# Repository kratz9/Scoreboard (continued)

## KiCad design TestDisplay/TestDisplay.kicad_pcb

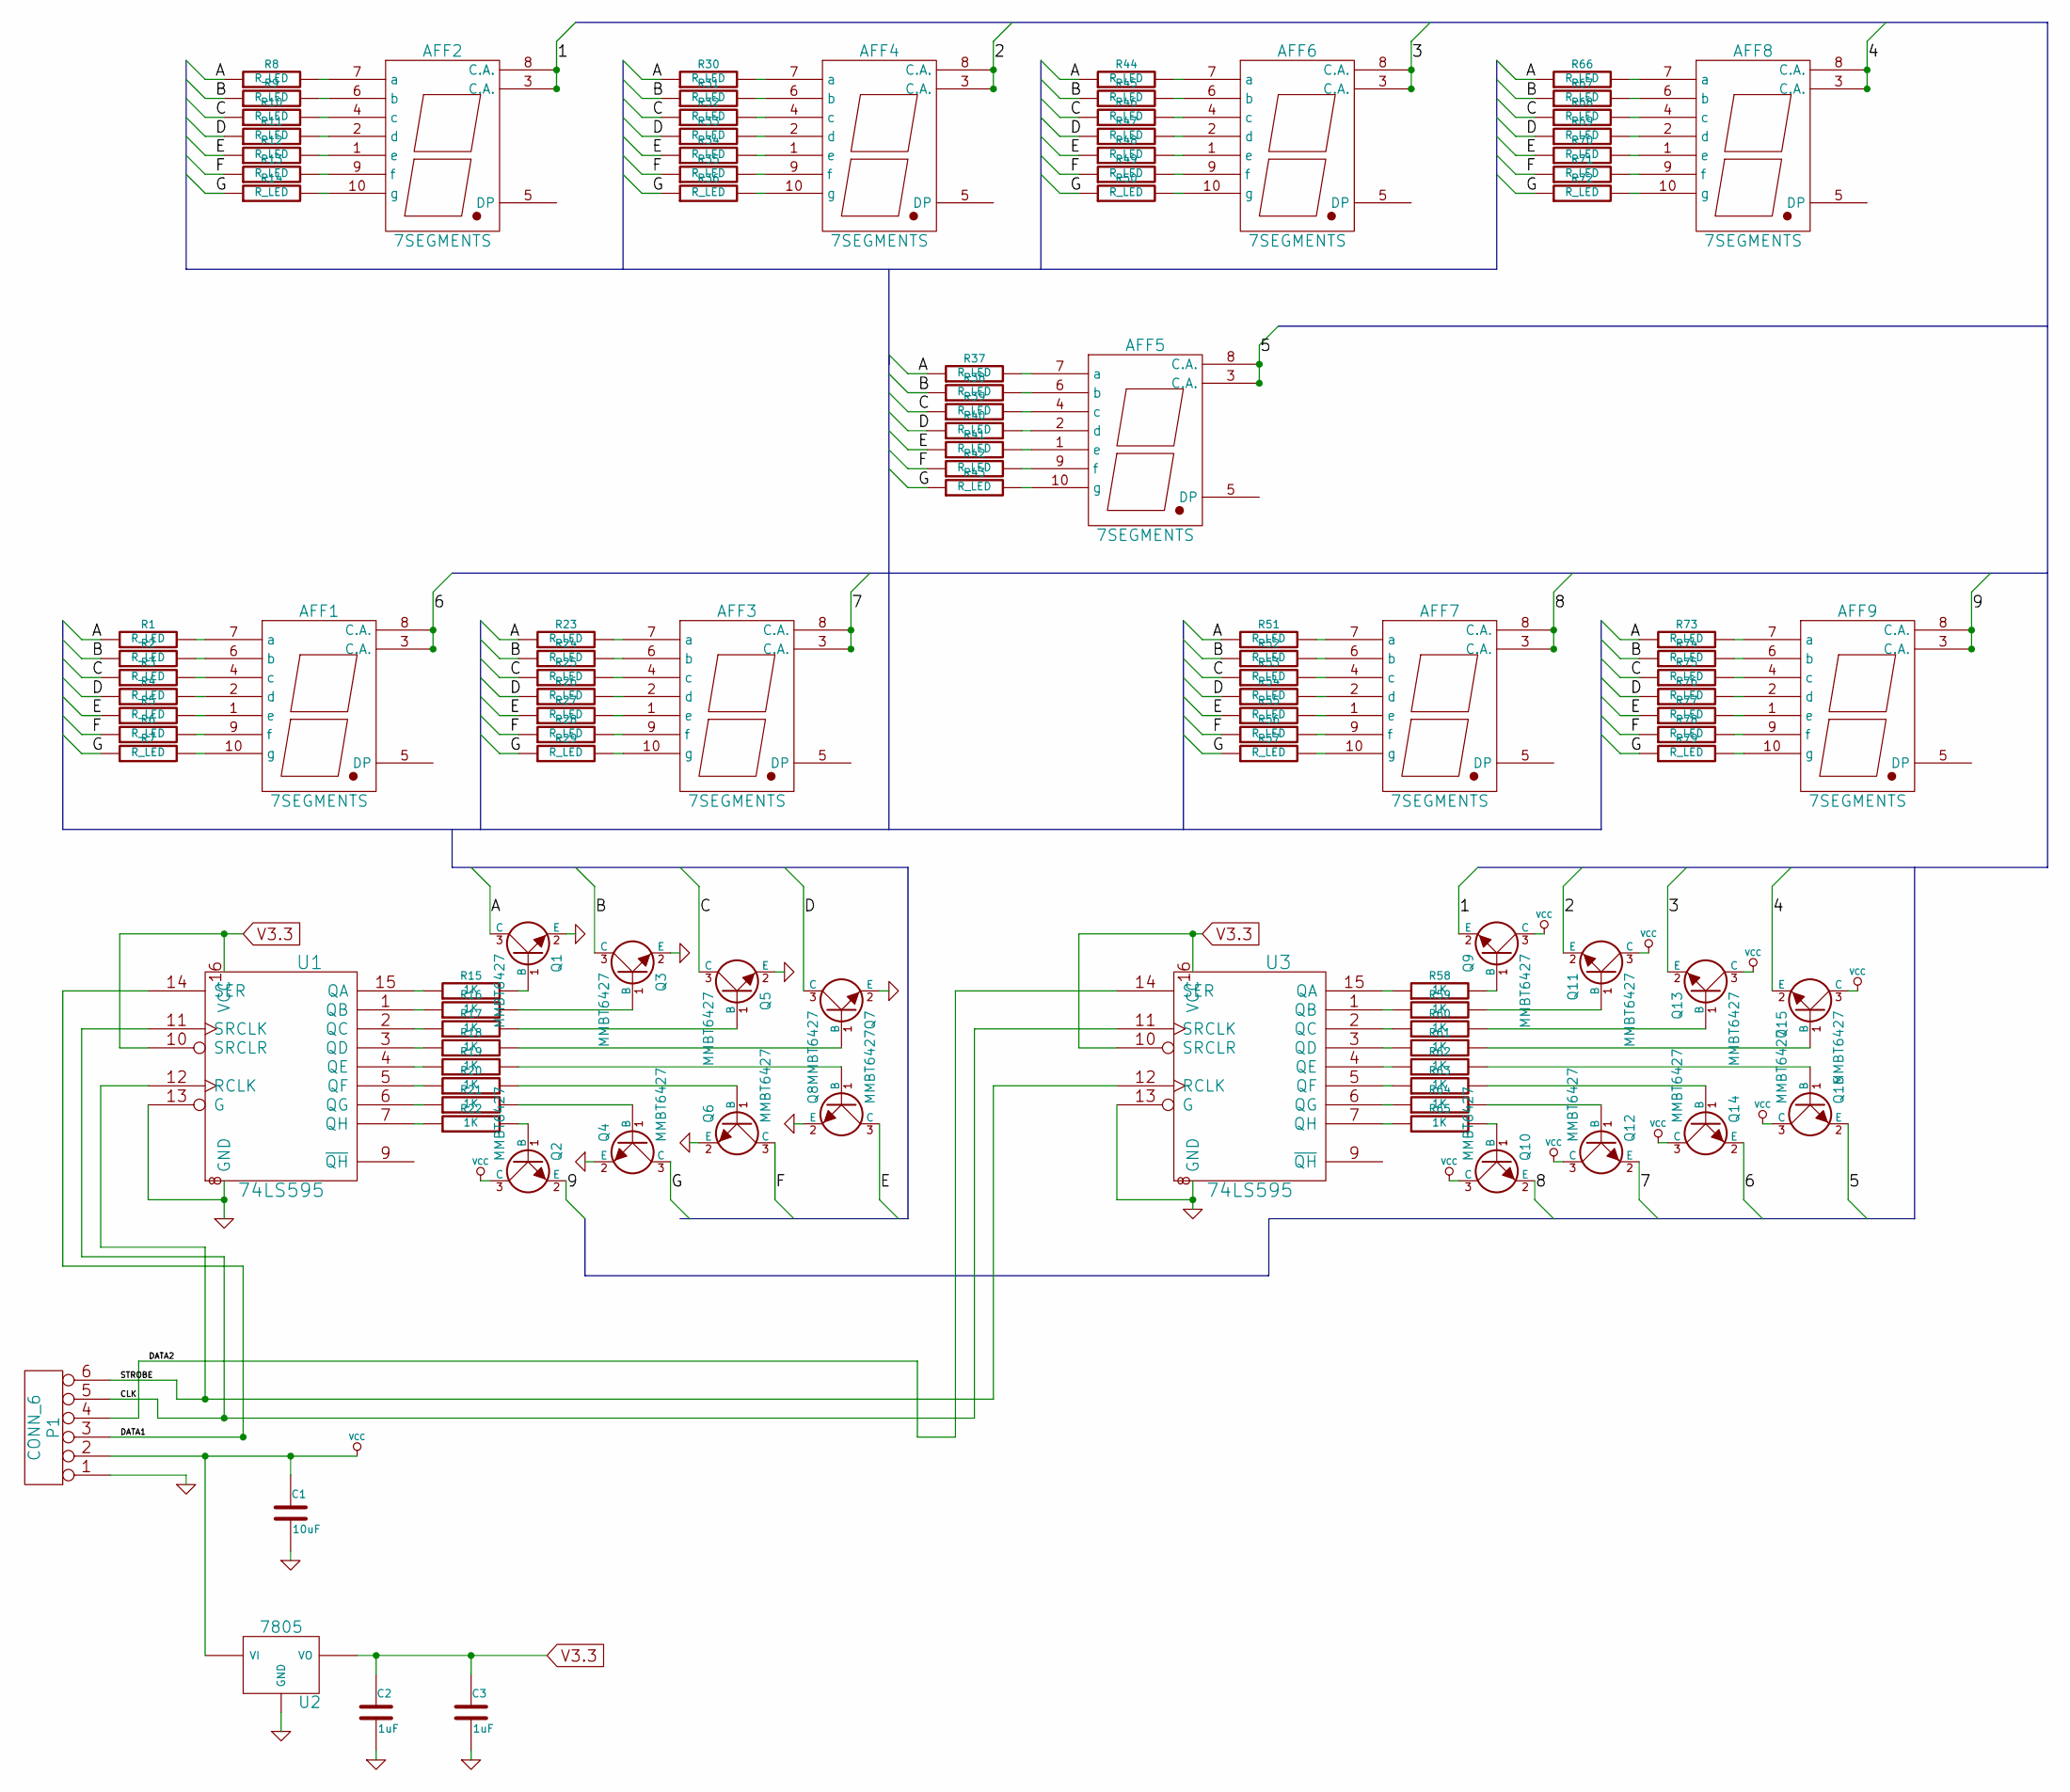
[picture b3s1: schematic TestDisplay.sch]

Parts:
AFF1, AFF2, AFF3, AFF4, AFF5, AFF6, AFF7, AFF8, AFF9: 7SEGMENTS
C1: 10uF
C2, C3: 1uF
P1: CONN_6
Q1, Q2, Q3, Q4, Q5, Q6, Q7, Q8, Q9, Q10, Q11, Q12, Q13, Q14, Q15, Q16: MMBT6427
R1, R2, R3, R4, R5, R6, R7, R8, R9, R10, R11, R12, R13, R14, R23, R24, R25, R26, R27, R28, R29, R30, R31, R32, R33, R34, R35, R36, R37, R38, R39, R40, R41, R42, R43, R44, R45, R46, R47, R48, R49, R50, R51, R52, R53, R54, R55, R56, R57, R66, R67, R68, R69, R70, R71, R72, R73, R74, R75, R76, R77, R78, R79: R_LED
R15, R16, R17, R18, R19, R20, R21, R22, R58, R59, R60, R61, R62, R63, R64, R65: 1K
U1, U3: 74LS595
U2: 7805

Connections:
/1: AFF2.3 (C.A.), AFF2.8 (C.A.), Q9.2 (E)
/2: AFF4.3 (C.A.), AFF4.8 (C.A.), Q11.2 (E)
/3: AFF6.3 (C.A.), AFF6.8 (C.A.), Q13.2 (E)
/4: AFF8.3 (C.A.), AFF8.8 (C.A.), Q15.2 (E)
/5: AFF5.3 (C.A.), AFF5.8 (C.A.), Q16.2 (E)
/6: AFF1.3 (C.A.), AFF1.8 (C.A.), Q14.2 (E)
/7: AFF3.3 (C.A.), AFF3.8 (C.A.), Q12.2 (E)
/8: AFF7.3 (C.A.), AFF7.8 (C.A.), Q10.2 (E)
/9: AFF9.3 (C.A.), AFF9.8 (C.A.), Q2.2 (E)
/A: Q1.3 (C), R1.1, R8.1, R23.1, R30.1, R37.1, R44.1, R51.1, R66.1, R73.1
/B: Q3.3 (C), R2.1, R9.1, R24.1, R31.1, R38.1, R45.1, R52.1, R67.1, R74.1
/C: Q5.3 (C), R3.1, R10.1, R25.1, R32.1, R39.1, R46.1, R53.1, R68.1, R75.1
/CLK: P1.5, U1.11 (SRCLK), U3.11 (SRCLK)
/D: Q7.3 (C), R4.1, R11.1, R26.1, R33.1, R40.1, R47.1, R54.1, R69.1, R76.1
/DATA1: P1.3, U1.14 (SER)
/DATA2: P1.4, U3.14 (SER)
/E: Q8.3 (C), R5.1, R12.1, R27.1, R34.1, R41.1, R48.1, R55.1, R70.1, R77.1
/F: Q6.3 (C), R6.1, R13.1, R28.1, R35.1, R42.1, R49.1, R56.1, R71.1, R78.1
/G: Q4.3 (C), R7.1, R14.1, R29.1, R36.1, R43.1, R50.1, R57.1, R72.1, R79.1
/STROBE: P1.6, U1.12 (RCLK), U3.12 (RCLK)
GND: C1.2, C2.2, C3.2, P1.1, Q1.2 (E), Q3.2 (E), Q4.2 (E), Q5.2 (E), Q6.2 (E), Q7.2 (E), Q8.2 (E), U1.8 (GND), U1.13 (G), U2.1, U2.GND, U3.8 (GND), U3.13 (G)
unnamed: AFF8.7 (a), R66.2
unnamed: AFF8.6 (b), R67.2
unnamed: AFF8.4 (c), R68.2
unnamed: AFF8.2 (d), R69.2
unnamed: AFF8.1 (e), R70.2
unnamed: AFF8.9 (f), R71.2
unnamed: AFF8.10 (g), R72.2
unnamed: AFF7.2 (d), R54.2
unnamed: AFF7.1 (e), R55.2
unnamed: AFF7.9 (f), R56.2
unnamed: AFF7.10 (g), R57.2
unnamed: AFF9.7 (a), R73.2
unnamed: AFF9.6 (b), R74.2
unnamed: AFF9.4 (c), R75.2
unnamed: AFF9.2 (d), R76.2
unnamed: AFF9.1 (e), R77.2
unnamed: AFF9.9 (f), R78.2
unnamed: AFF9.10 (g), R79.2
unnamed: AFF7.4 (c), R53.2
unnamed: AFF1.10 (g), R7.2
unnamed: AFF5.4 (c), R39.2
unnamed: AFF5.2 (d), R40.2
unnamed: AFF5.1 (e), R41.2
unnamed: AFF5.9 (f), R42.2
unnamed: AFF5.10 (g), R43.2
unnamed: AFF1.7 (a), R1.2
unnamed: AFF1.6 (b), R2.2
unnamed: AFF1.4 (c), R3.2
unnamed: AFF1.2 (d), R4.2
unnamed: AFF1.1 (e), R5.2
unnamed: AFF1.9 (f), R6.2
unnamed: AFF3.7 (a), R23.2
unnamed: AFF3.6 (b), R24.2
unnamed: AFF3.4 (c), R25.2
unnamed: AFF3.2 (d), R26.2
unnamed: AFF3.1 (e), R27.2
unnamed: AFF3.9 (f), R28.2
unnamed: AFF3.10 (g), R29.2
unnamed: AFF7.7 (a), R51.2
unnamed: AFF7.6 (b), R52.2
unnamed: Q13.1 (B), R60.2
unnamed: Q15.1 (B), R61.2
unnamed: Q16.1 (B), R62.2
unnamed: Q14.1 (B), R63.2
unnamed: Q12.1 (B), R64.2
unnamed: Q10.1 (B), R65.2
unnamed: Q11.1 (B), R59.2
unnamed: Q9.1 (B), R58.2
unnamed: R59.1, U3.1 (QB)
unnamed: R60.1, U3.2 (QC)
unnamed: R61.1, U3.3 (QD)
unnamed: R62.1, U3.4 (QE)
unnamed: R63.1, U3.5 (QF)
unnamed: R64.1, U3.6 (QG)
unnamed: R65.1, U3.7 (QH)
unnamed: R58.1, U3.15 (QA)
unnamed: Q1.1 (B), R15.2
unnamed: Q3.1 (B), R16.2
unnamed: Q5.1 (B), R17.2
unnamed: R19.1, U1.4 (QE)
unnamed: Q8.1 (B), R19.2
unnamed: R20.1, U1.5 (QF)
unnamed: Q6.1 (B), R20.2
unnamed: R21.1, U1.6 (QG)
unnamed: Q4.1 (B), R21.2
unnamed: R22.1, U1.7 (QH)
unnamed: Q2.1 (B), R22.2
unnamed: R15.1, U1.15 (QA)
unnamed: R16.1, U1.1 (QB)
unnamed: R17.1, U1.2 (QC)
unnamed: R18.1, U1.3 (QD)
unnamed: Q7.1 (B), R18.2
unnamed: AFF5.6 (b), R38.2
unnamed: AFF2.10 (g), R14.2
unnamed: AFF2.7 (a), R8.2
unnamed: AFF2.6 (b), R9.2
unnamed: AFF2.4 (c), R10.2
unnamed: AFF2.2 (d), R11.2
unnamed: AFF2.1 (e), R12.2
unnamed: AFF2.9 (f), R13.2
unnamed: AFF4.1 (e), R34.2
unnamed: AFF4.2 (d), R33.2
unnamed: AFF4.4 (c), R32.2
unnamed: AFF4.6 (b), R31.2
unnamed: AFF4.7 (a), R30.2
unnamed: AFF4.9 (f), R35.2
unnamed: AFF4.10 (g), R36.2
unnamed: AFF5.7 (a), R37.2
unnamed: AFF6.7 (a), R44.2
unnamed: AFF6.6 (b), R45.2
unnamed: AFF6.4 (c), R46.2
unnamed: AFF6.2 (d), R47.2
unnamed: AFF6.1 (e), R48.2
unnamed: AFF6.9 (f), R49.2
unnamed: AFF6.10 (g), R50.2
V3.3: C2.1, C3.1, U1.10 (SRCLR), U1.16 (VCC), U2.3, U2.VO, U3.10 (SRCLR), U3.16 (VCC)
VCC: C1.1, P1.2, Q2.3 (C), Q9.3 (C), Q10.3 (C), Q11.3 (C), Q12.3 (C), Q13.3 (C), Q14.3 (C), Q15.3 (C), Q16.3 (C), U2.2, U2.VI

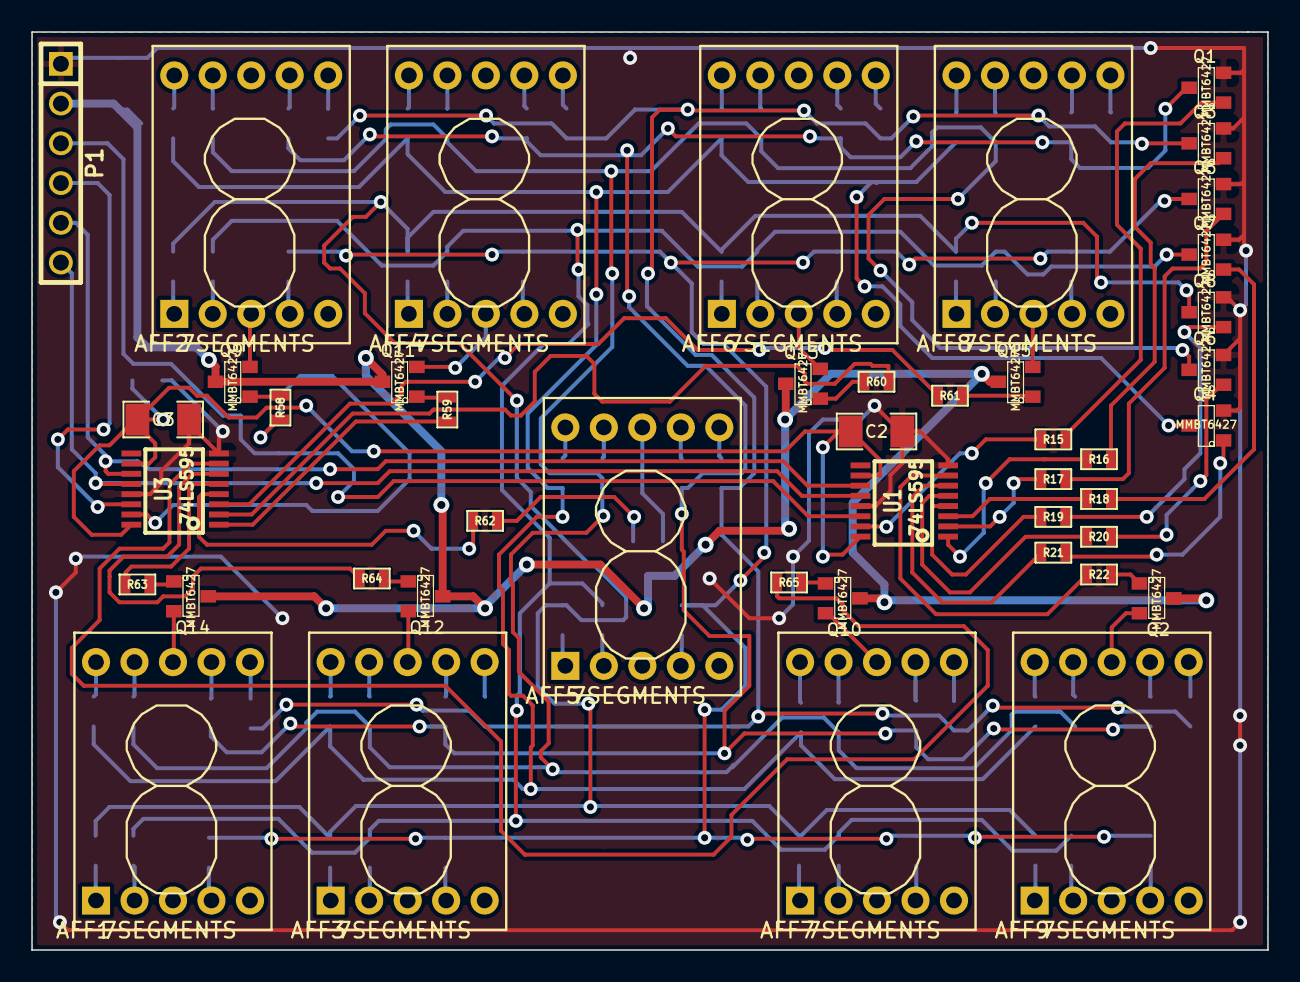
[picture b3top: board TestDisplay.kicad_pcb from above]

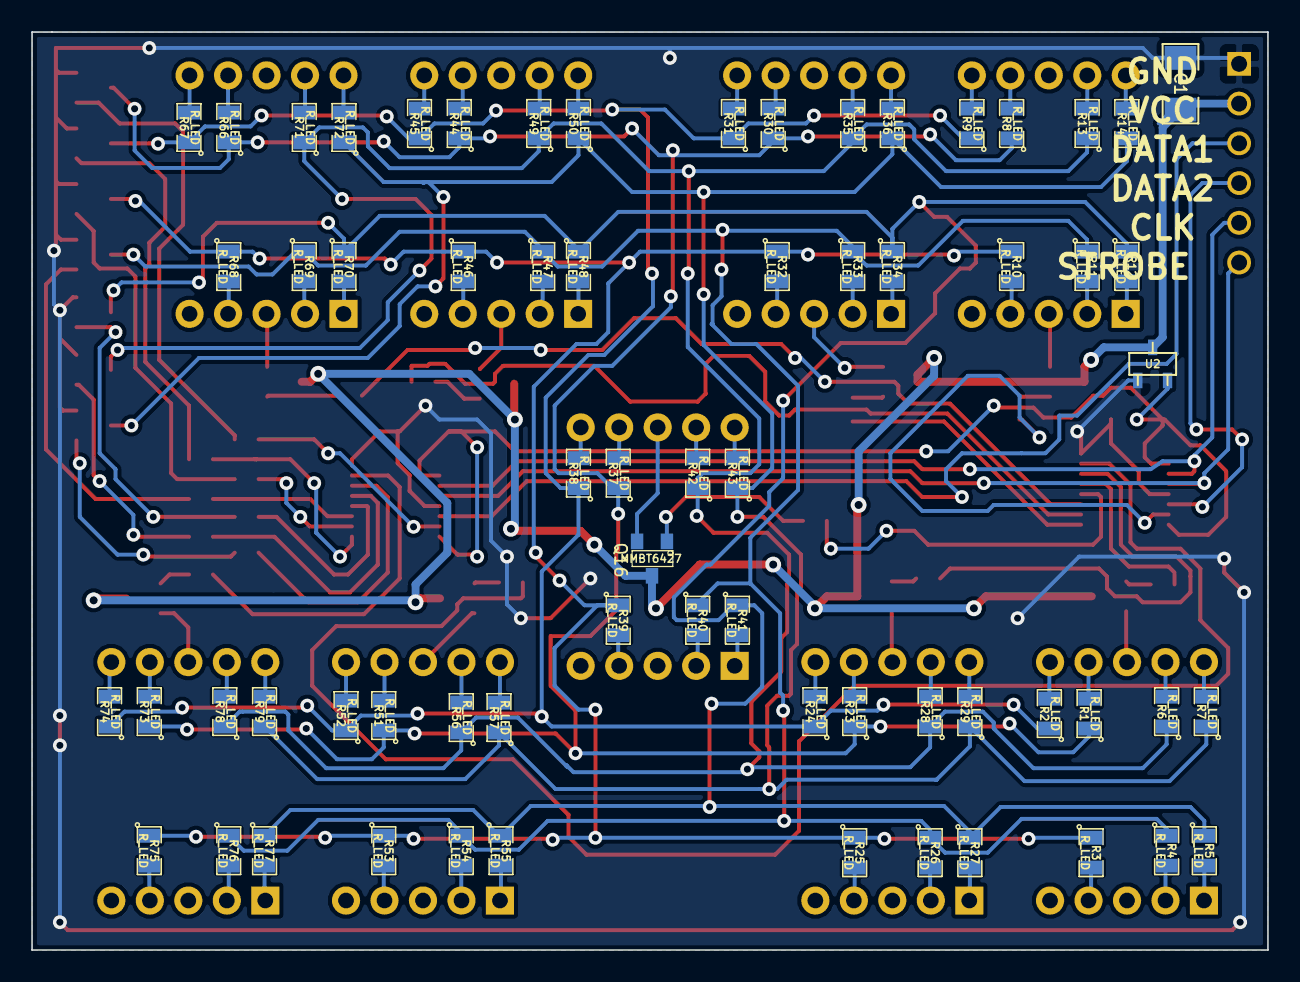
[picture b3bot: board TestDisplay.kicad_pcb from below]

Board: 2 copper layers, 79.0 x 58.7 mm, 111 parts (66 on the bottom side), 118 nets.

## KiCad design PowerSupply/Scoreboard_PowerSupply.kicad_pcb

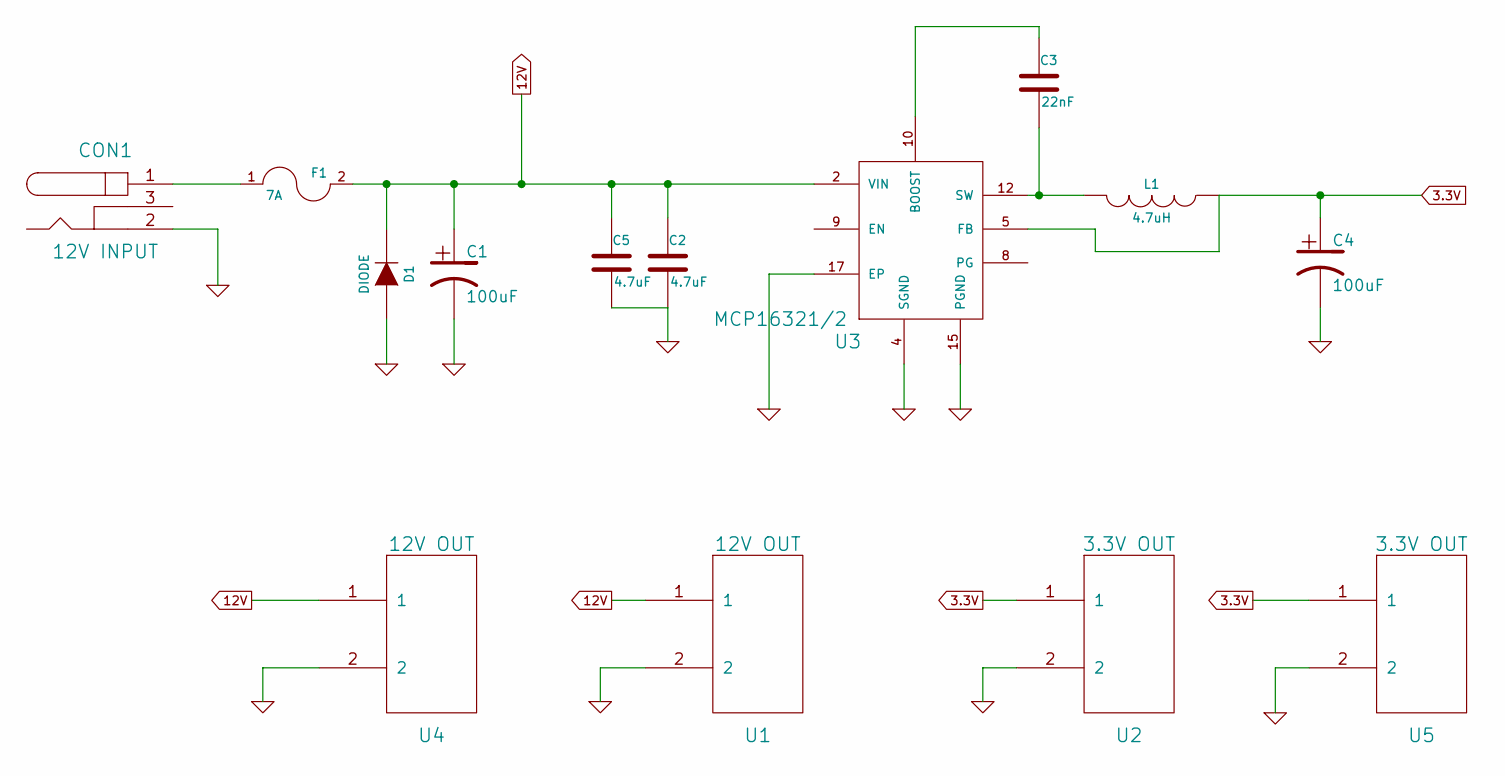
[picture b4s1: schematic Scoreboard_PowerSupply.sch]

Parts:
C1, C4: 100uF
C2, C5: 4.7uF
C3: 22nF
CON1: 12V INPUT
D1: DIODE
F1: 7A
L1: 4.7uH
U1, U4: 12V OUT
U2, U5: 3.3V OUT
U3: MCP16321/2

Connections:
3.3V: C4.1, L1.1, U2.1, U3.5 (FB), U5.1
12V: C1.1, C2.1, C5.1, D1.2 (K), F1.2, U1.1, U3.2 (VIN), U4.1
GND: C1.2, C2.2, C4.2, C5.2, CON1.2, D1.1 (A), U1.2, U2.2, U3.4 (SGND), U3.15 (PGND), U3.17 (EP), U4.2, U5.2
unnamed: C3.1, U3.10 (BOOST)
unnamed: C3.2, L1.2, U3.12 (SW)
unnamed: CON1.1, F1.1

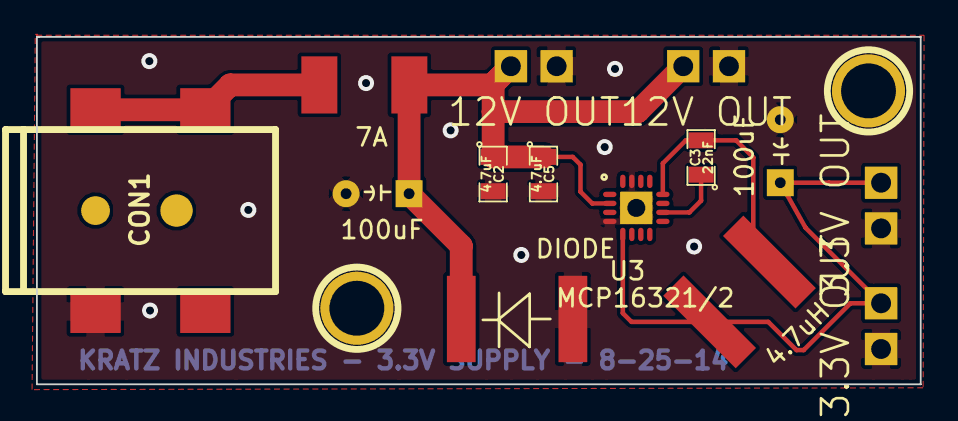
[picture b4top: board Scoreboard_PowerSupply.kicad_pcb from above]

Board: 2 copper layers, 49.1 x 19.3 mm, 16 parts (0 on the bottom side), 6 nets.

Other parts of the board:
1PIN, 1PIN#2: P***; 1pin

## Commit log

2014-07-22 Initial
2014-08-21 Added System Diagram
2014-08-21 Made Sheets Started Driver Circuit
2014-08-23 Documentation
2014-08-23 Minor revisions and project stuff
2014-08-25 8-24
    Started separating out the power supply and building the PCB
2014-08-25 8-25
2014-08-26 8-25 10:02
2014-08-26 8-26-14
2014-09-05 9-4
    Changing the LED drive to Opto-coupled
2014-09-17 9-16
2014-09-26 Finallizing LED Driver
2014-09-26 Still finalizng LED Driver
2014-10-02 10-2-14
2015-01-25 Test display start
2015-01-26 Revert "Test display start"
    This reverts commit c1fec8fd228401c8c95fc62cf6add0c17674f68f.
2015-01-26 Revert "Revert "Test display start""
    This reverts commit fc41cdbdcf2d1a7a8f10e923f753cbc016b450d2.
2015-01-26 Deleted wrong file
2015-01-26 Test display
2015-01-27 Daily
2015-02-01 Test Display Finished
2015-02-06 start of test digit
2015-02-06 Digit PCB
2015-02-24 Digit Fixes
2015-02-26 Solder Paste Layer Export
